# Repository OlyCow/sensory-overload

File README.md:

sensory-overload
================

The design files for our custom sensor board.

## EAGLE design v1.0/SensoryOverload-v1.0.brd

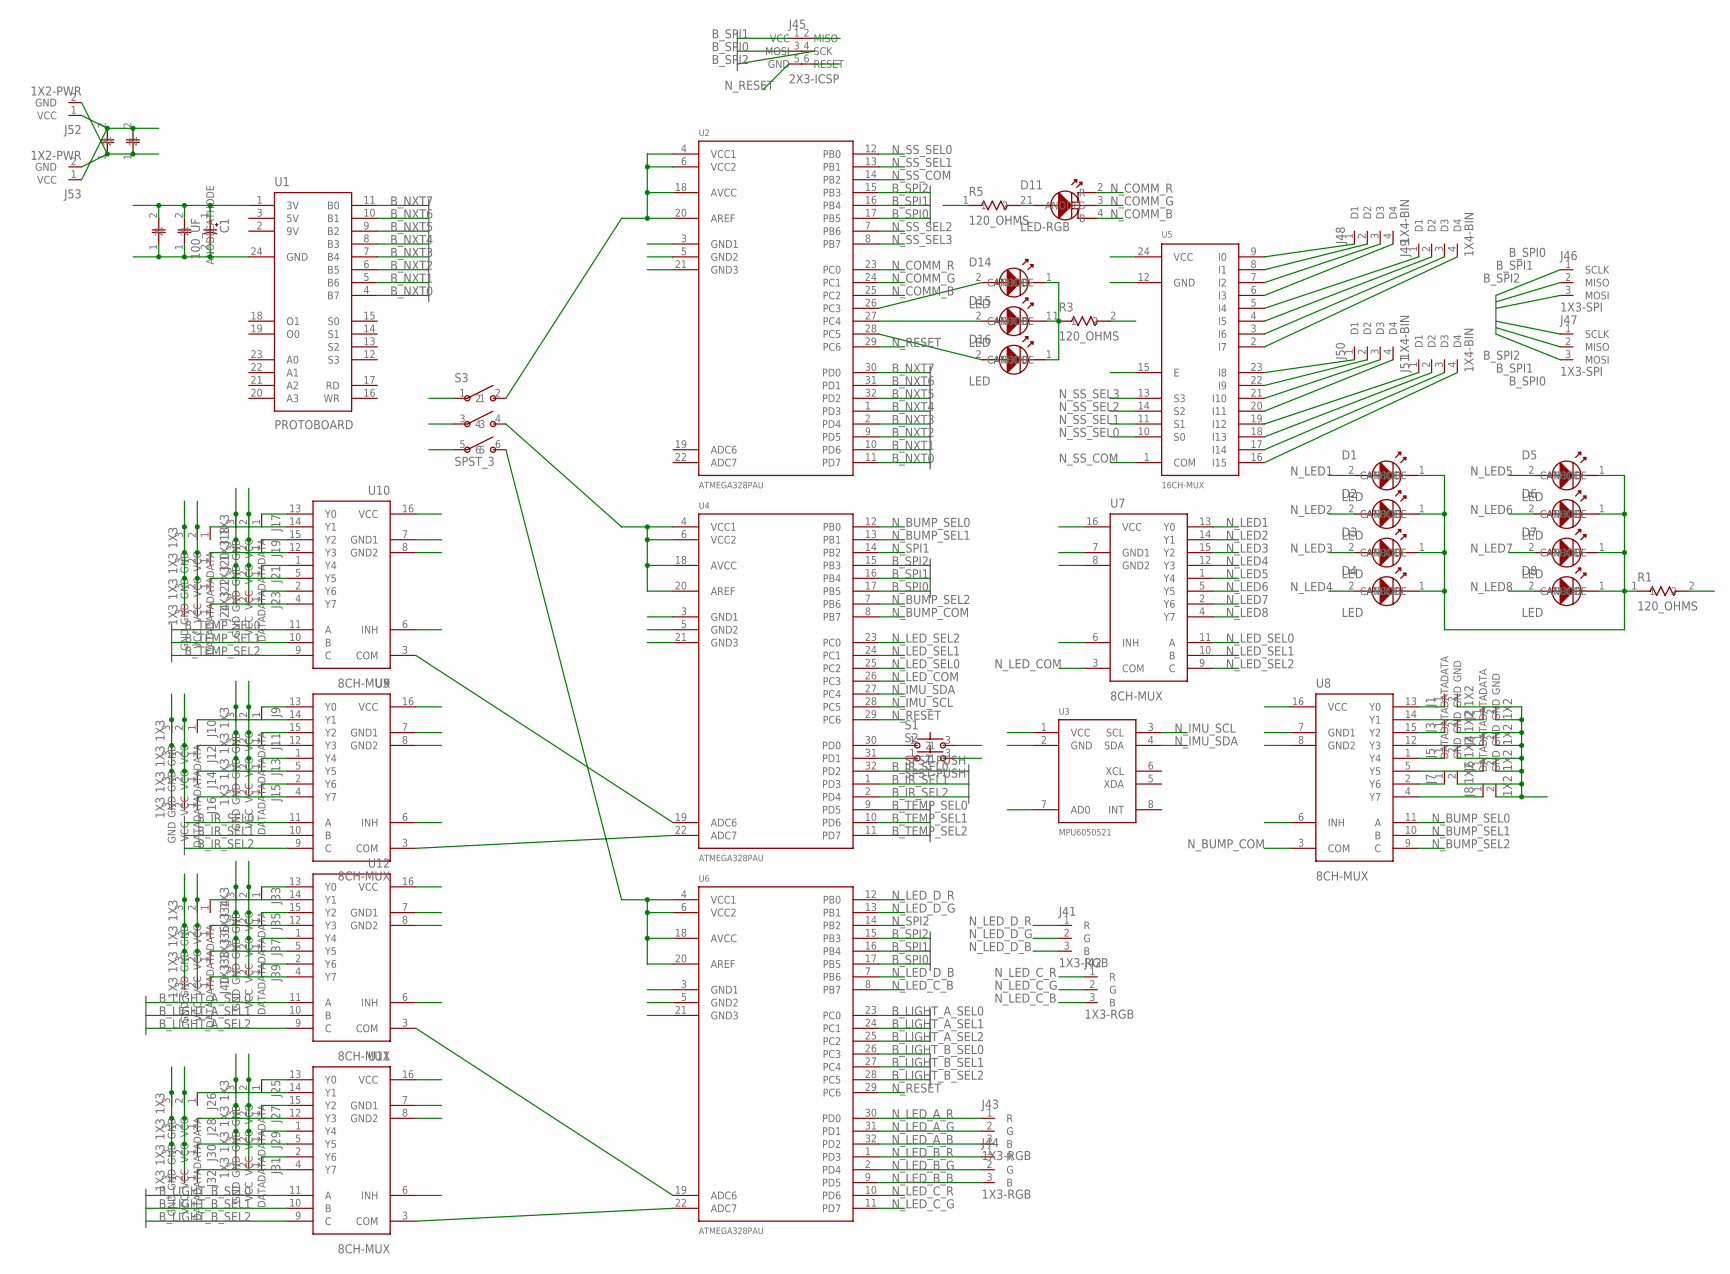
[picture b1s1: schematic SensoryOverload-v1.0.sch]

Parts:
C1: 100_UF; AVE-D
C2, C5: 0.1_UF; 0603
C3, C4: 10_PF; 0603
D1, D2, D3, D4, D5, D6, D7, D8, D14, D15, D16: LED; 0603
D11: LED-RGB; PLCC4
J1, J2, J3, J4, J5, J6, J7, J8: 1X2
J9, J10, J11, J12, J13, J14, J15, J16, J17, J18, J19, J20, J21, J22, J23, J24, J25, J26, J27, J28, J29, J30, J31, J32, J33, J34, J35, J36, J37, J38, J39, J40: 1X3
J41, J42, J43, J44: 1X3-RGB; 1X3
J45: 2X3-ICSP; 2X3
J46, J47: 1X3-SPI; 1X3
J48, J49, J50, J51: 1X4-BIN; 1X4
J52, J53: 1X2-PWR; 1X2
R1, R3, R5: 120_OHMS; 0603
S1, S2: SPST-PUSH; SMD
S3: SPST_3; DIP_3
U1: PROTOBOARD; HEADER
U2, U4, U6: ATMEGA328PAU; TQFP32
U3: MPU6050521; BREAKOUT
U5: 16CH-MUX; SOIC24
U7, U8, U9, U10, U11, U12: 8CH-MUX; TSSOP16

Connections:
B_IR_SEL0: U4.32 (PD2), U9.11 (A)
B_IR_SEL1: U4.1 (PD3), U9.10 (B)
B_IR_SEL2: U4.2 (PD4), U9.9 (C)
B_LIGHT_A_SEL0: U6.23 (PC0), U12.11 (A)
B_LIGHT_A_SEL1: U6.24 (PC1), U12.10 (B)
B_LIGHT_A_SEL2: U6.25 (PC2), U12.9 (C)
B_LIGHT_B_SEL0: U6.26 (PC3), U11.11 (A)
B_LIGHT_B_SEL1: U6.27 (PC4), U11.10 (B)
B_LIGHT_B_SEL2: U6.28 (PC5), U11.9 (C)
B_NXT0: U1.4 (B7), U2.11 (PD7)
B_NXT1: U1.5 (B6), U2.10 (PD6)
B_NXT2: U1.6 (B5), U2.9 (PD5)
B_NXT3: U1.7 (B4), U2.2 (PD4)
B_NXT4: U1.8 (B3), U2.1 (PD3)
B_NXT5: U1.9 (B2), U2.32 (PD2)
B_NXT6: U1.10 (B1), U2.31 (PD1)
B_NXT7: U1.11 (B0), U2.30 (PD0)
B_SPI0: J45.3 (SCK), J46.1 (SCLK), J47.1 (SCLK), U2.17 (PB5), U4.17 (PB5), U6.17 (PB5)
B_SPI1: J45.1 (MISO), J46.2 (MISO), J47.2 (MISO), U2.16 (PB4), U4.16 (PB4), U6.16 (PB4)
B_SPI2: J45.4 (MOSI), J46.3 (MOSI), J47.3 (MOSI), U2.15 (PB3), U4.15 (PB3), U6.15 (PB3)
B_TEMP_SEL0: U4.9 (PD5), U10.11 (A)
B_TEMP_SEL1: U4.10 (PD6), U10.10 (B)
B_TEMP_SEL2: U4.11 (PD7), U10.9 (C)
GND1: U4.3 (GND1), U6.3 (GND1)
GND2: U4.5 (GND2), U6.5 (GND2)
GND3: U4.21 (GND3), U6.21 (GND3)
N_BUMP0: J1.1 (DATA), U8.13 (Y0)
N_BUMP1: J2.1 (DATA), U8.14 (Y1)
N_BUMP2: J3.1 (DATA), U8.15 (Y2)
N_BUMP3: J4.1 (DATA), U8.12 (Y3)
N_BUMP4: J5.1 (DATA), U8.1 (Y4)
N_BUMP5: J6.1 (DATA), U8.5 (Y5)
N_BUMP6: J7.1 (DATA), U8.2 (Y6)
N_BUMP7: J8.1 (DATA), U8.4 (Y7)
N_BUMP_COM: U4.8 (PB7), U8.3 (COM)
N_BUMP_SEL0: U4.12 (PB0), U8.11 (A)
N_BUMP_SEL1: U4.13 (PB1), U8.10 (B)
N_BUMP_SEL2: U4.7 (PB6), U8.9 (C)
N_COMM_B: D11.4 (B), U2.25 (PC2)
N_COMM_G: D11.3 (G), U2.24 (PC1)
N_COMM_R: D11.2 (R), U2.23 (PC0)
N_GND: C1.2 (CATHODE), C2.1, C3.1, C4.1, C5.1, J1.2 (GND), J2.2 (GND), J3.2 (GND), J4.2 (GND), J5.2 (GND), J6.2 (GND), J7.2 (GND), J8.2 (GND), J9.3 (GND), J10.3 (GND), J11.3 (GND), J12.3 (GND), J13.3 (GND), J14.3 (GND), J15.3 (GND), J16.3 (GND), J17.3 (GND), J18.3 (GND), J19.3 (GND), J20.3 (GND), J21.3 (GND), J22.3 (GND), J23.3 (GND), J24.3 (GND), J25.3 (GND), J26.3 (GND), J27.3 (GND), J28.3 (GND), J29.3 (GND), J30.3 (GND), J31.3 (GND), J32.3 (GND), J33.3 (GND), J34.3 (GND), J35.3 (GND), J36.3 (GND), J37.3 (GND), J38.3 (GND), J39.3 (GND), J40.3 (GND), J45.6 (GND), J52.2 (GND), J53.2 (GND), R1.2, R3.2, S1.3 (2), S2.3 (2), U1.24 (GND), U2.3 (GND1), U2.5 (GND2), U2.21 (GND3), U3.2 (GND), U3.7 (AD0), U5.12 (GND), U5.15 (E), U7.6 (INH), U7.7 (GND1), U7.8 (GND2), U8.6 (INH), U8.7 (GND1), U8.8 (GND2), U9.6 (INH), U9.7 (GND1), U9.8 (GND2), U10.6 (INH), U10.7 (GND1), U10.8 (GND2), U11.6 (INH), U11.7 (GND1), U11.8 (GND2), U12.6 (INH), U12.7 (GND1), U12.8 (GND2)
N_IMU_SCL: U3.3 (SCL), U4.28 (PC5)
N_IMU_SDA: U3.4 (SDA), U4.27 (PC4)
N_IR0: J9.1 (DATA), U9.13 (Y0)
N_IR1: J10.1 (DATA), U9.14 (Y1)
N_IR2: J11.1 (DATA), U9.15 (Y2)
N_IR3: J12.1 (DATA), U9.12 (Y3)
N_IR4: J13.1 (DATA), U9.1 (Y4)
N_IR5: J14.1 (DATA), U9.5 (Y5)
N_IR6: J15.1 (DATA), U9.2 (Y6)
N_IR7: J16.1 (DATA), U9.4 (Y7)
N_IR_COM: U4.22 (ADC7), U9.3 (COM)
N_LED1: D1.2 (ANODE), U7.13 (Y0)
N_LED2: D2.2 (ANODE), U7.14 (Y1)
N_LED3: D3.2 (ANODE), U7.15 (Y2)
N_LED4: D4.2 (ANODE), U7.12 (Y3)
N_LED5: D5.2 (ANODE), U7.1 (Y4)
N_LED6: D6.2 (ANODE), U7.5 (Y5)
N_LED7: D7.2 (ANODE), U7.2 (Y6)
N_LED8: D8.2 (ANODE), U7.4 (Y7)
N_LED_A_B: J43.3 (B), U6.32 (PD2)
N_LED_A_G: J43.2 (G), U6.31 (PD1)
N_LED_A_R: J43.1 (R), U6.30 (PD0)
N_LED_B_B: J44.3 (B), U6.9 (PD5)
N_LED_B_G: J44.2 (G), U6.2 (PD4)
N_LED_B_R: J44.1 (R), U6.1 (PD3)
N_LED_COM: U4.26 (PC3), U7.3 (COM)
N_LED_COMM_A: D14.1 (CATHODE), D15.1 (CATHODE), D16.1 (CATHODE), R3.1
N_LED_COMM_B: D11.1 (ANODE), R5.2
N_LED_C_B: J42.3 (B), U6.8 (PB7)
N_LED_C_G: J42.2 (G), U6.11 (PD7)
N_LED_C_R: J42.1 (R), U6.10 (PD6)
N_LED_D_B: J41.3 (B), U6.7 (PB6)
N_LED_D_G: J41.2 (G), U6.13 (PB1)
N_LED_D_R: J41.1 (R), U6.12 (PB0)
N_LED_GND: D1.1 (CATHODE), D2.1 (CATHODE), D3.1 (CATHODE), D4.1 (CATHODE), D5.1 (CATHODE), D6.1 (CATHODE), D7.1 (CATHODE), D8.1 (CATHODE), R1.1
N_LED_SEL0: U4.25 (PC2), U7.11 (A)
N_LED_SEL1: U4.24 (PC1), U7.10 (B)
N_LED_SEL2: U4.23 (PC0), U7.9 (C)
N_LIGHT_A0: J33.1 (DATA), U12.13 (Y0)
N_LIGHT_A1: J34.1 (DATA), U12.14 (Y1)
N_LIGHT_A2: J35.1 (DATA), U12.15 (Y2)
N_LIGHT_A3: J36.1 (DATA), U12.12 (Y3)
N_LIGHT_A4: J37.1 (DATA), U12.1 (Y4)
N_LIGHT_A5: J38.1 (DATA), U12.5 (Y5)
N_LIGHT_A6: J39.1 (DATA), U12.2 (Y6)
N_LIGHT_A7: J40.1 (DATA), U12.4 (Y7)
N_LIGHT_A_COM: U12.3 (COM)
N_LIGHT_B0: J25.1 (DATA), U11.13 (Y0)
N_LIGHT_B1: J26.1 (DATA), U11.14 (Y1)
N_LIGHT_B2: J27.1 (DATA), U11.15 (Y2)
N_LIGHT_B3: J28.1 (DATA), U11.12 (Y3)
N_LIGHT_B4: J29.1 (DATA), U11.1 (Y4)
N_LIGHT_B5: J30.1 (DATA), U11.5 (Y5)
N_LIGHT_B6: J31.1 (DATA), U11.2 (Y6)
N_LIGHT_B7: J32.1 (DATA), U11.4 (Y7)
N_LIGHT_B_COM: U11.3 (COM)
N_PUSH0: S1.1, U4.30 (PD0)
N_PUSH1: S2.1, U4.31 (PD1)
N_RESET: J45.5 (RESET), U2.29 (PC6), U4.29 (PC6), U6.29 (PC6)
N_SPI1: J48.1 (D1), U4.14 (PB2), U5.9 (I0)
N_SPI2: J48.2 (D2), U5.8 (I1), U6.14 (PB2)
N_SPI3: J48.3 (D3), U5.7 (I2)
N_SPI4: J48.4 (D4), U5.6 (I3)
N_SPI5: J49.1 (D1), U5.5 (I4)
N_SPI6: J49.2 (D2), U5.4 (I5)
N_SPI7: J49.3 (D3), U5.3 (I6)
N_SPI8: J49.4 (D4), U5.2 (I7)
N_SPI9: J50.1 (D1), U5.23 (I8)
N_SPI10: J50.2 (D2), U5.22 (I9)
N_SPI11: J50.3 (D3), U5.21 (I10)
N_SPI12: J50.4 (D4), U5.20 (I11)
N_SPI13: J51.1 (D1), U5.19 (I12)
N_SPI14: J51.2 (D2), U5.18 (I13)
N_SPI15: J51.3 (D3), U5.17 (I14)
N_SPI16: J51.4 (D4), U5.16 (I15)
N_SS_COM: U2.14 (PB2), U5.1 (COM)
N_SS_SEL0: U2.12 (PB0), U5.10 (S0)
N_SS_SEL1: U2.13 (PB1), U5.11 (S1)
N_SS_SEL2: U2.7 (PB6), U5.14 (S2)
N_SS_SEL3: U2.8 (PB7), U5.13 (S3)
N_STATUS_LED0: D14.2 (ANODE), U2.26 (PC3)
N_STATUS_LED1: D15.2 (ANODE), U2.27 (PC4)
N_STATUS_LED2: D16.2 (ANODE), U2.28 (PC5)
N_TEMP0: J17.1 (DATA), U10.13 (Y0)
N_TEMP1: J18.1 (DATA), U10.14 (Y1)
N_TEMP2: J19.1 (DATA), U10.15 (Y2)
N_TEMP3: J20.1 (DATA), U10.12 (Y3)
N_TEMP4: J21.1 (DATA), U10.1 (Y4)
N_TEMP5: J22.1 (DATA), U10.5 (Y5)
N_TEMP6: J23.1 (DATA), U10.2 (Y6)
N_TEMP7: J24.1 (DATA), U10.4 (Y7)
N_TEMP_COM: U4.19 (ADC6), U10.3 (COM)
N_VCC: C1.1 (ANODE), C2.2, C3.2, C4.2, C5.2, J9.2 (VCC), J10.2 (VCC), J11.2 (VCC), J12.2 (VCC), J13.2 (VCC), J14.2 (VCC), J15.2 (VCC), J16.2 (VCC), J17.2 (VCC), J18.2 (VCC), J19.2 (VCC), J20.2 (VCC), J21.2 (VCC), J22.2 (VCC), J23.2 (VCC), J24.2 (VCC), J25.2 (VCC), J26.2 (VCC), J27.2 (VCC), J28.2 (VCC), J29.2 (VCC), J30.2 (VCC), J31.2 (VCC), J32.2 (VCC), J33.2 (VCC), J34.2 (VCC), J35.2 (VCC), J36.2 (VCC), J37.2 (VCC), J38.2 (VCC), J39.2 (VCC), J40.2 (VCC), J45.2 (VCC), J52.1 (VCC), J53.1 (VCC), R5.1, S3.1, S3.3, S3.5, U1.1 (3V), U3.1 (VCC), U5.24 (VCC), U7.16 (VCC), U8.16 (VCC), U9.16 (VCC), U10.16 (VCC), U11.16 (VCC), U12.16 (VCC)
N_VCC_MCU0: S3.2, U2.4 (VCC1), U2.6 (VCC2), U2.18 (AVCC), U2.20 (AREF)
N_VCC_MCU1: S3.4, U4.4 (VCC1), U4.6 (VCC2), U4.18 (AVCC), U4.20 (AREF)
N_VCC_MCU2: S3.6, U6.4 (VCC1), U6.6 (VCC2), U6.18 (AVCC), U6.20 (AREF)

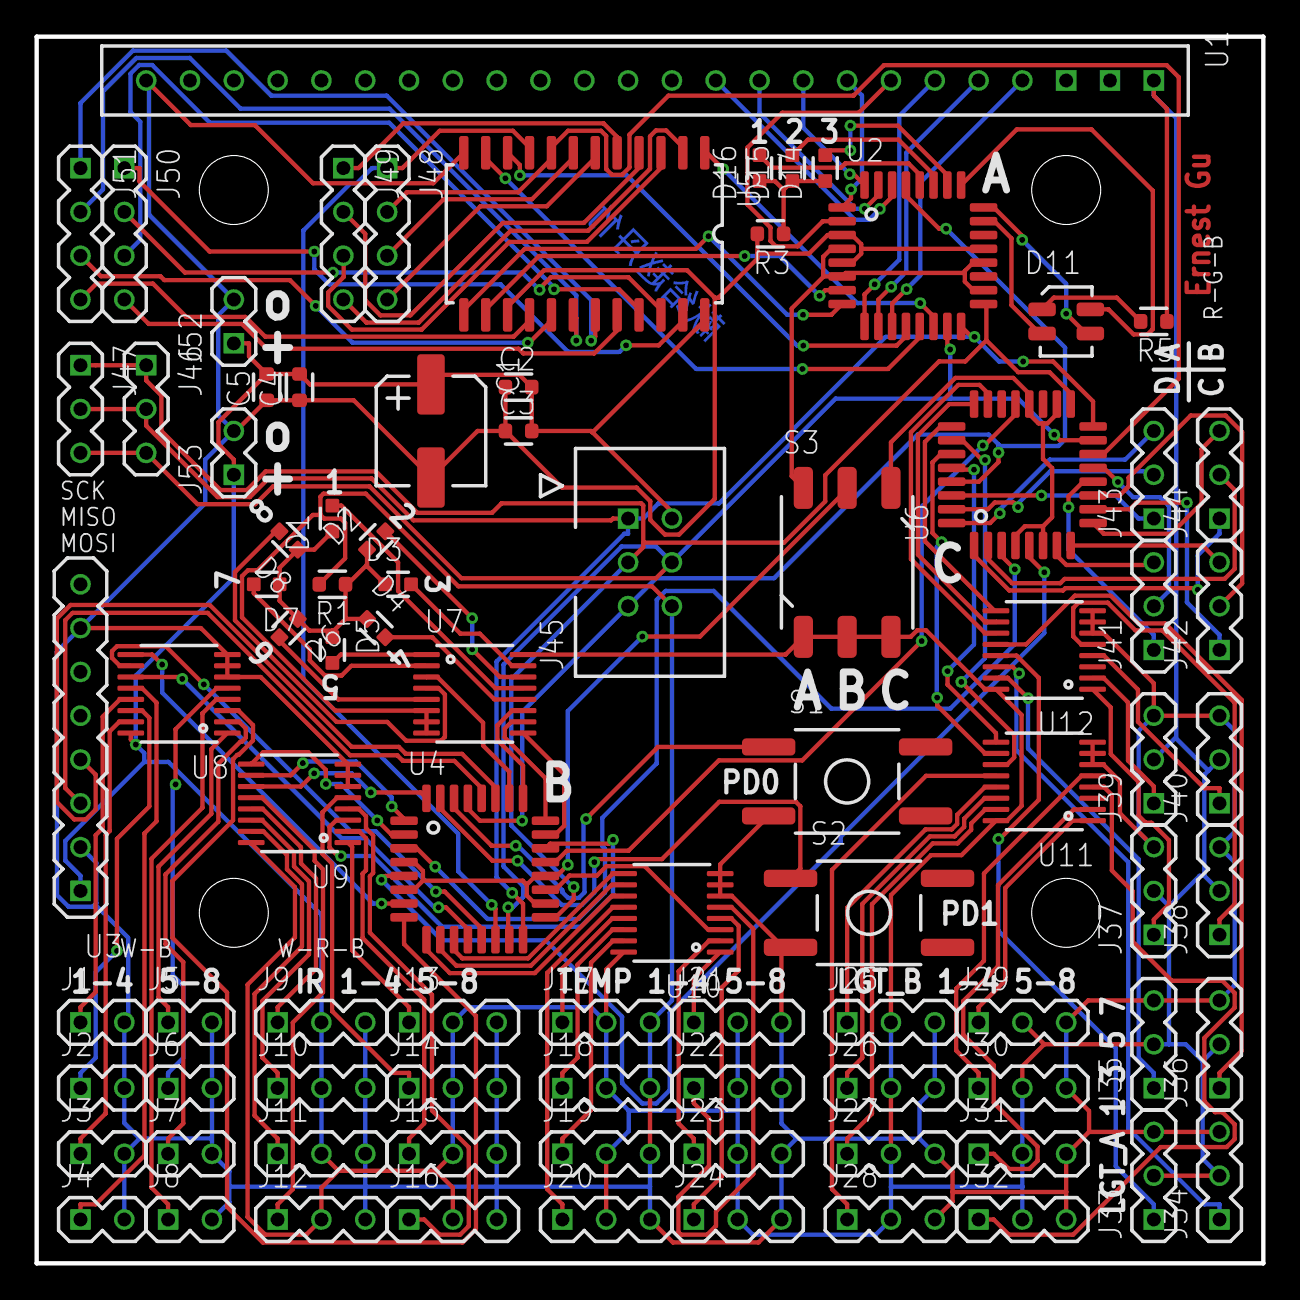
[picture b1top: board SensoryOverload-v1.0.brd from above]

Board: 2 copper layers, 71.1 x 71.1 mm, 97 parts (0 on the bottom side), 136 nets.

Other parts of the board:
U$1, U$2, U$3, U$4: STANDOFF
U$5: DEDICATION
U$6: LOGO-OLYCOW
U$7: SLOGAN-OLYCOW
U$8: LOGO-OSHW
U$9: LOGO-GITHUB

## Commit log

2014-05-18 Added board and schematic for v1.0
2014-05-18 Added gerbers for v1.0
